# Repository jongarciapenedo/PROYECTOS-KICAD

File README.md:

# PROYECTOS-KICAD
Compendio de circuitos electrónicos hechos en kicad

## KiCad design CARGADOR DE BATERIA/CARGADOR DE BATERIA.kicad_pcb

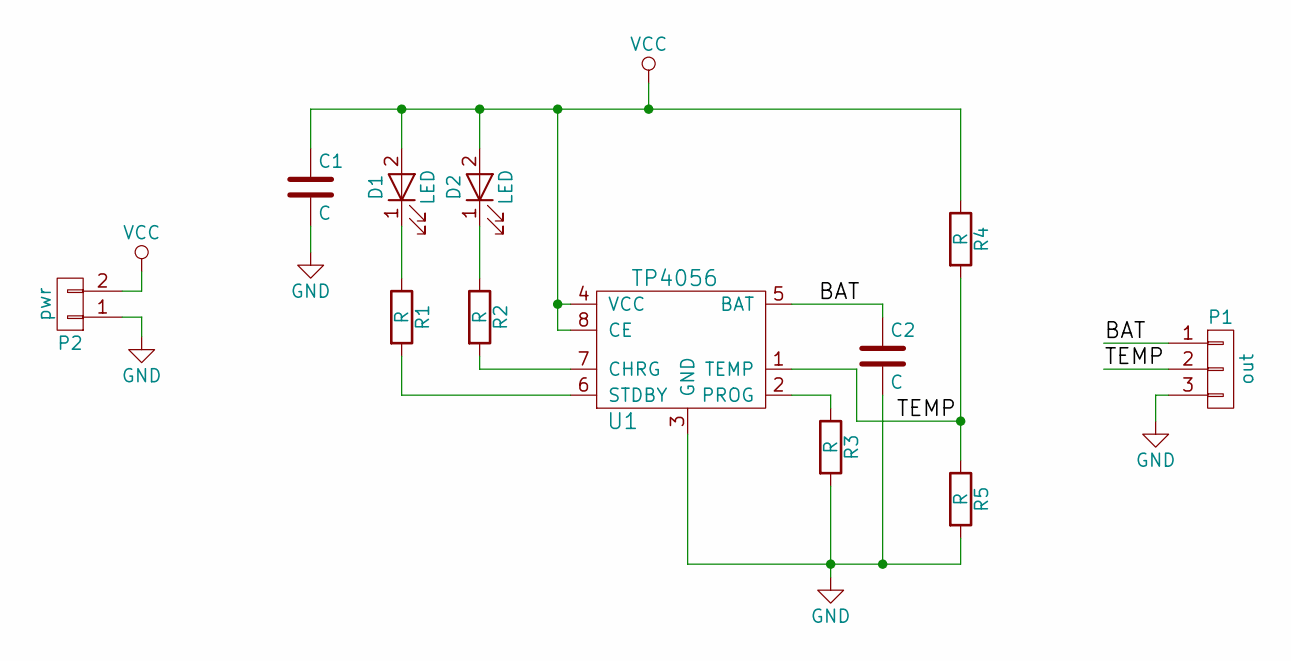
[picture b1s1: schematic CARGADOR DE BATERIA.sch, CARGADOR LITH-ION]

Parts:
C1, C2: C; C_Disc_D3_P2.5
D1, D2: LED; LED-3MM
P1: out; Pin_Header_Straight_1x03
P2: pwr; Pin_Header_Straight_1x02
R1, R2, R3, R4, R5: R; Resistor_Horizontal_RM7mmJJ
U1: TP4056; SOP8

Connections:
/BAT: C2.1, P1.1, U1.5 (BAT)
/TEMP: P1.2, R4.2, R5.1, U1.1 (TEMP)
GND: C1.2, C2.2, P1.3, P2.1, R3.2, R5.2, U1.3 (GND)
unnamed: D1.1 (K), R1.1
unnamed: D2.1 (K), R2.1
unnamed: R1.2, U1.6 (STDBY)
unnamed: R2.2, U1.7 (CHRG)
unnamed: R3.1, U1.2 (PROG)
VCC: C1.1, D1.2 (A), D2.2 (A), P2.2, R4.1, U1.4 (VCC), U1.8 (CE)

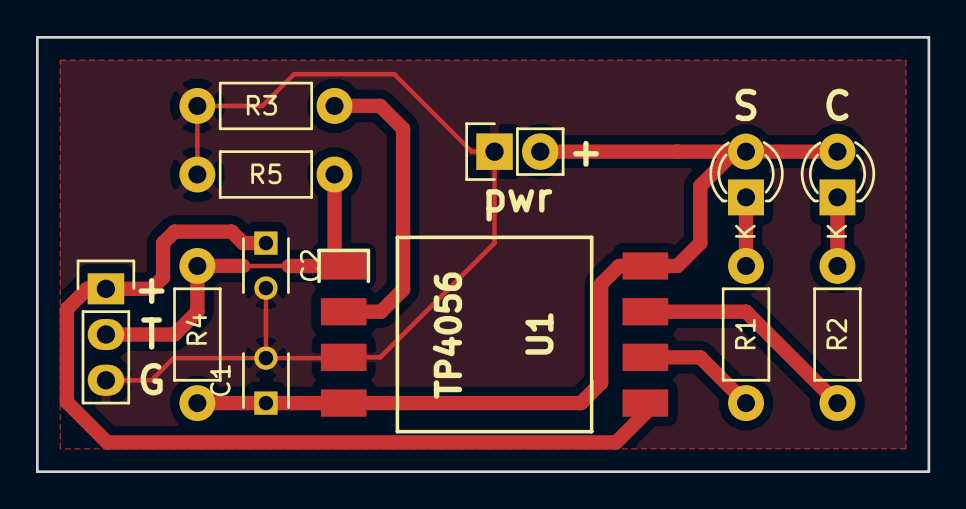
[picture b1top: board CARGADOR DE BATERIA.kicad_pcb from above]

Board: 2 copper layers, 49.5 x 24.1 mm, 12 parts (0 on the bottom side), 9 nets.

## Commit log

2017-07-06 Cargador de baterios lithion
2017-07-06 agregando ignore
2017-07-06 agregando el pcb
2017-07-06 arreglando la tierra
